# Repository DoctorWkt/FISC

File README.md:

# FISC: An 8-bit TTL CPU with a Stack Register

**Please note**: The FISC design has some major flaws. Rather than
fix them, I've incorporated the fixes into the next version of the
design: .

FISC is an 8-bit microseqenced CPU wth a 64K address space built from
discrete TTL-level components. It provides:

 + recursive **F**unctions,
 + **I**ndexed addressing and
 + **S**tack operations

as well as the usual load/store and arithmetic operations, comparisons,
branches and jumps.

The design uses 25 chips and has 8K of ROM, 56K of RAM and a UART.

## Documentation

The overall design of the CPU is covered in
[Docs/arch_overview.md](Docs/arch_overview.md), and some details
of the expected hardware implementation are in 
[Docs/fisc_implementation.md](Docs/fisc_implementation.md).

## Implementation

At present, I have:

 + a Perl CPU simulator, [csim](csim)
 + an assembler, [cas](cas)
 + a simple compiler, [clc](clc)
 + example assembly and higher-level programs in [Examples](Examples)
 + a Verilog design in [Verilog](Verilog)
 + a schematic in [Kicad/schematic.pdf](Kicad/schematic.pdf)

## Status of the CPU

**mid-June, 2020**: I've ordered PCBs and they have arrived and I've soldered
on all the components. The CPU passes most of the tests but I have an issue
with addition that I am still working on.

For more detail on progress, you can read my [journal](Docs/journal.md).

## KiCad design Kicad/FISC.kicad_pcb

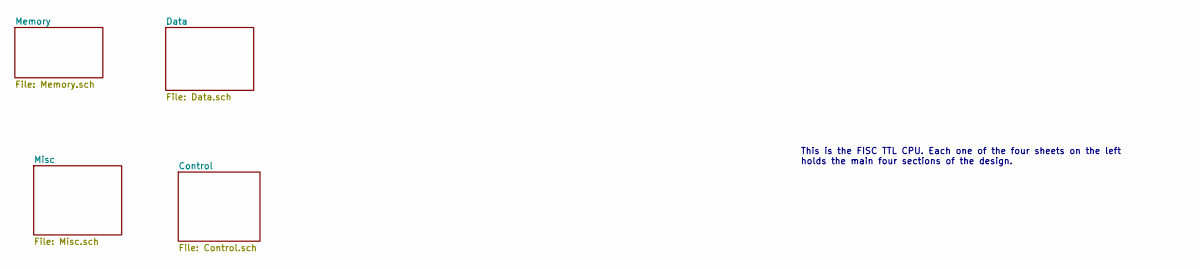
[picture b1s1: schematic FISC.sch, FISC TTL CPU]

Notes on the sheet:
This is the FISC TTL CPU. Each one of the four sheets on the left holds the main four sections of the design.

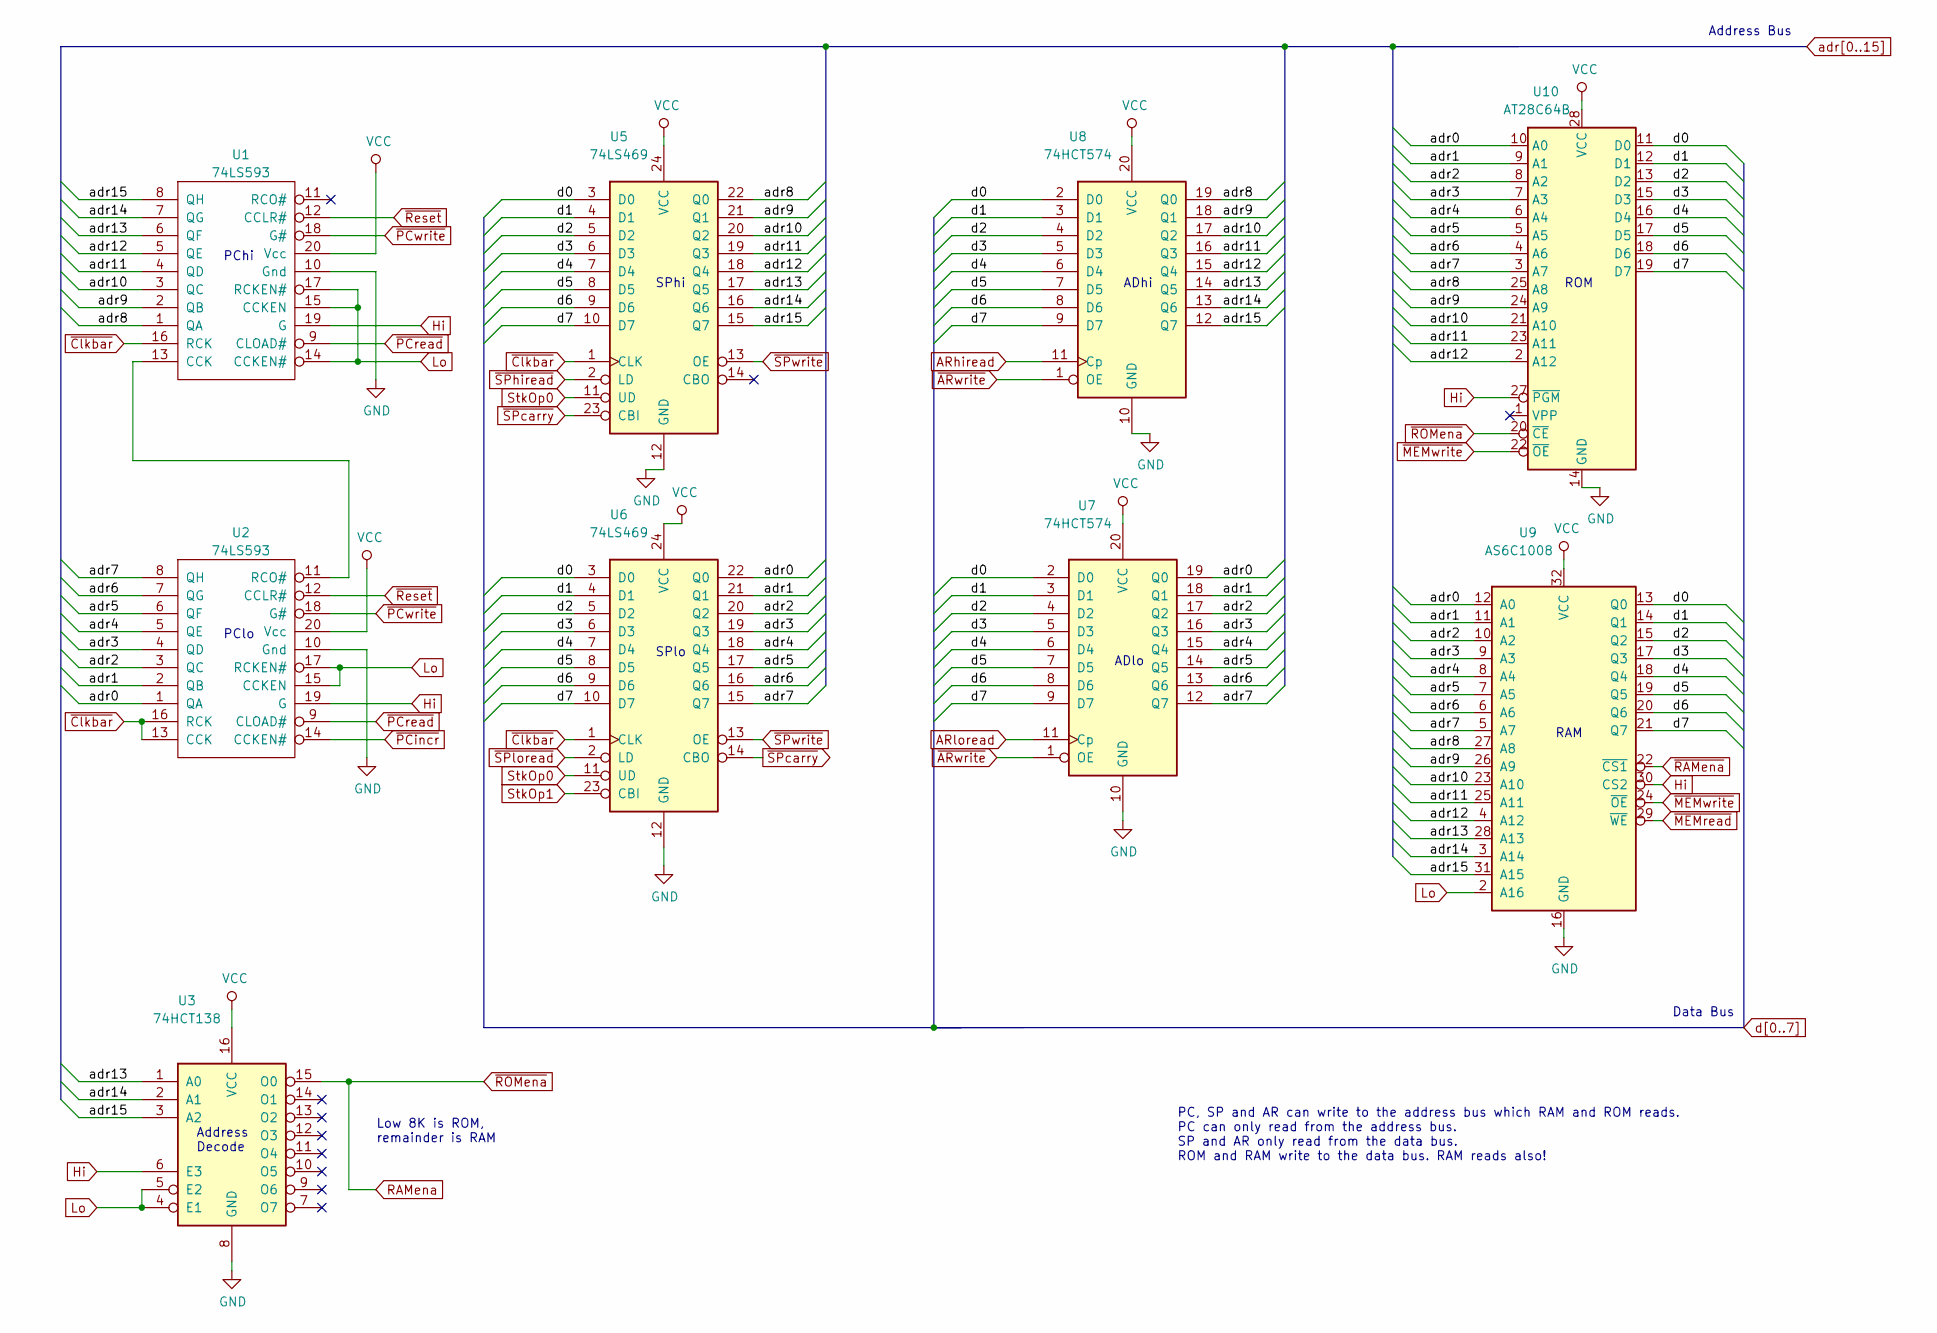
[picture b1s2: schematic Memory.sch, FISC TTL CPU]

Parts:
U1, U2: 74LS593; DIP-20_W7.62mm_Socket
U3: 74HCT138; SOIC-16_3.9x9.9mm_P1.27mm
U5, U6: 74LS469; DIP-24_W7.62mm
U7, U8: 74HCT574; SOIC-20W_7.5x12.8mm_P1.27mm
U9: AS6C1008; DIP-32_W15.24mm
U10: AT28C64B; DIP-28_W15.24mm

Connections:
ARhiread: U8.11 (Cp); also elsewhere on the board
ARloread: U7.11 (Cp); also elsewhere on the board
Hi: U1.19 (G), U1.20 (Vcc), U2.19 (G), U2.20 (Vcc), U3.6 (E3), U3.16 (VCC), U5.24 (VCC), U6.24 (VCC), U7.20 (VCC), U8.20 (VCC), U9.30 (CS2), U9.32 (VCC), U10.27 (~PGM), U10.28 (VCC); also elsewhere on the board
Lo: U1.10 (Gnd), U1.14 (CCKEN#), U1.15 (CCKEN), U1.17 (RCKEN#), U2.10 (Gnd), U2.15 (CCKEN), U2.17 (RCKEN#), U3.4 (E1), U3.5 (E2), U3.8 (GND), U5.12 (GND), U6.12 (GND), U7.10 (GND), U8.10 (GND), U9.2 (A16), U9.16 (GND), U10.14 (GND); also elsewhere on the board
unnamed: U1.13 (CCK), U2.11 (RCO#)
RAMena: U3.15 (O0), U10.20 (~CE); also elsewhere on the board
StkOp0: U5.11 (UD), U6.11 (UD); also elsewhere on the board
StkOp1: U6.23 (CBI); also elsewhere on the board
adr0: U2.1 (QA), U6.22 (Q0), U7.19 (Q0), U9.12 (A0), U10.10 (A0); also elsewhere on the board
adr1: U2.2 (QB), U6.21 (Q1), U7.18 (Q1), U9.11 (A1), U10.9 (A1); also elsewhere on the board
adr2: U2.3 (QC), U6.20 (Q2), U7.17 (Q2), U9.10 (A2), U10.8 (A2); also elsewhere on the board
adr3: U2.4 (QD), U6.19 (Q3), U7.16 (Q3), U9.9 (A3), U10.7 (A3); also elsewhere on the board
adr4: U2.5 (QE), U6.18 (Q4), U7.15 (Q4), U9.8 (A4), U10.6 (A4); also elsewhere on the board
adr5: U2.6 (QF), U6.17 (Q5), U7.14 (Q5), U9.7 (A5), U10.5 (A5); also elsewhere on the board
adr6: U2.7 (QG), U6.16 (Q6), U7.13 (Q6), U9.6 (A6), U10.4 (A6); also elsewhere on the board
adr7: U2.8 (QH), U6.15 (Q7), U7.12 (Q7), U9.5 (A7), U10.3 (A7); also elsewhere on the board
adr8: U1.1 (QA), U5.22 (Q0), U8.19 (Q0), U9.27 (A8), U10.25 (A8); also elsewhere on the board
adr9: U1.2 (QB), U5.21 (Q1), U8.18 (Q1), U9.26 (A9), U10.24 (A9); also elsewhere on the board
adr10: U1.3 (QC), U5.20 (Q2), U8.17 (Q2), U9.23 (A10), U10.21 (A10); also elsewhere on the board
adr11: U1.4 (QD), U5.19 (Q3), U8.16 (Q3), U9.25 (A11), U10.23 (A11); also elsewhere on the board
adr12: U1.5 (QE), U5.18 (Q4), U8.15 (Q4), U9.4 (A12), U10.2 (A12); also elsewhere on the board
adr13: U1.6 (QF), U3.1 (A0), U5.17 (Q5), U8.14 (Q5), U9.28 (A13); also elsewhere on the board
adr14: U1.7 (QG), U3.2 (A1), U5.16 (Q6), U8.13 (Q6), U9.3 (A14); also elsewhere on the board
adr15: U1.8 (QH), U3.3 (A2), U5.15 (Q7), U8.12 (Q7), U9.31 (A15); also elsewhere on the board
d0: U5.3 (D0), U6.3 (D0), U7.2 (D0), U8.2 (D0), U9.13 (Q0), U10.11 (D0); also elsewhere on the board
d1: U5.4 (D1), U6.4 (D1), U7.3 (D1), U8.3 (D1), U9.14 (Q1), U10.12 (D1); also elsewhere on the board
d2: U5.5 (D2), U6.5 (D2), U7.4 (D2), U8.4 (D2), U9.15 (Q2), U10.13 (D2); also elsewhere on the board
d3: U5.6 (D3), U6.6 (D3), U7.5 (D3), U8.5 (D3), U9.17 (Q3), U10.15 (D3); also elsewhere on the board
d4: U5.7 (D4), U6.7 (D4), U7.6 (D4), U8.6 (D4), U9.18 (Q4), U10.16 (D4); also elsewhere on the board
d5: U5.8 (D5), U6.8 (D5), U7.7 (D5), U8.7 (D5), U9.19 (Q5), U10.17 (D5); also elsewhere on the board
d6: U5.9 (D6), U6.9 (D6), U7.8 (D6), U8.8 (D6), U9.20 (Q6), U10.18 (D6); also elsewhere on the board
d7: U5.10 (D7), U6.10 (D7), U7.9 (D7), U8.9 (D7), U9.21 (Q7), U10.19 (D7); also elsewhere on the board
~ARwrite: U7.1 (OE), U8.1 (OE); also elsewhere on the board
~Clkbar: U1.16 (RCK), U2.13 (CCK), U2.16 (RCK), U5.1 (CLK), U6.1 (CLK); also elsewhere on the board
~MEMread: U9.29 (~WE); also elsewhere on the board
~MEMwrite: U9.24 (~OE), U10.22 (~OE); also elsewhere on the board
~PCincr: U2.14 (CCKEN#); also elsewhere on the board
~PCread: U1.9 (CLOAD#), U2.9 (CLOAD#); also elsewhere on the board
~PCwrite: U1.18 (G#), U2.18 (G#); also elsewhere on the board
~RAMena: U9.22 (~CS1); also elsewhere on the board
~Reset: U1.12 (CCLR#), U2.12 (CCLR#); also elsewhere on the board
~SPcarry: U5.23 (CBI), U6.14 (CBO)
~SPhiread: U5.2 (LD); also elsewhere on the board
~SPloread: U6.2 (LD); also elsewhere on the board
~SPwrite: U5.13 (OE), U6.13 (OE); also elsewhere on the board

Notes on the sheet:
RAM
ROM
ADhi
ADlo
SPhi
SPlo
PChi
PClo
Address Decode
Address Bus
Data Bus
Low 8K is ROM, remainder is RAM
PC, SP and AR can write to the address bus which RAM and ROM reads. PC can only read from the address bus. SP and AR only read from the data bus. ROM and RAM write to the data bus. RAM reads also!

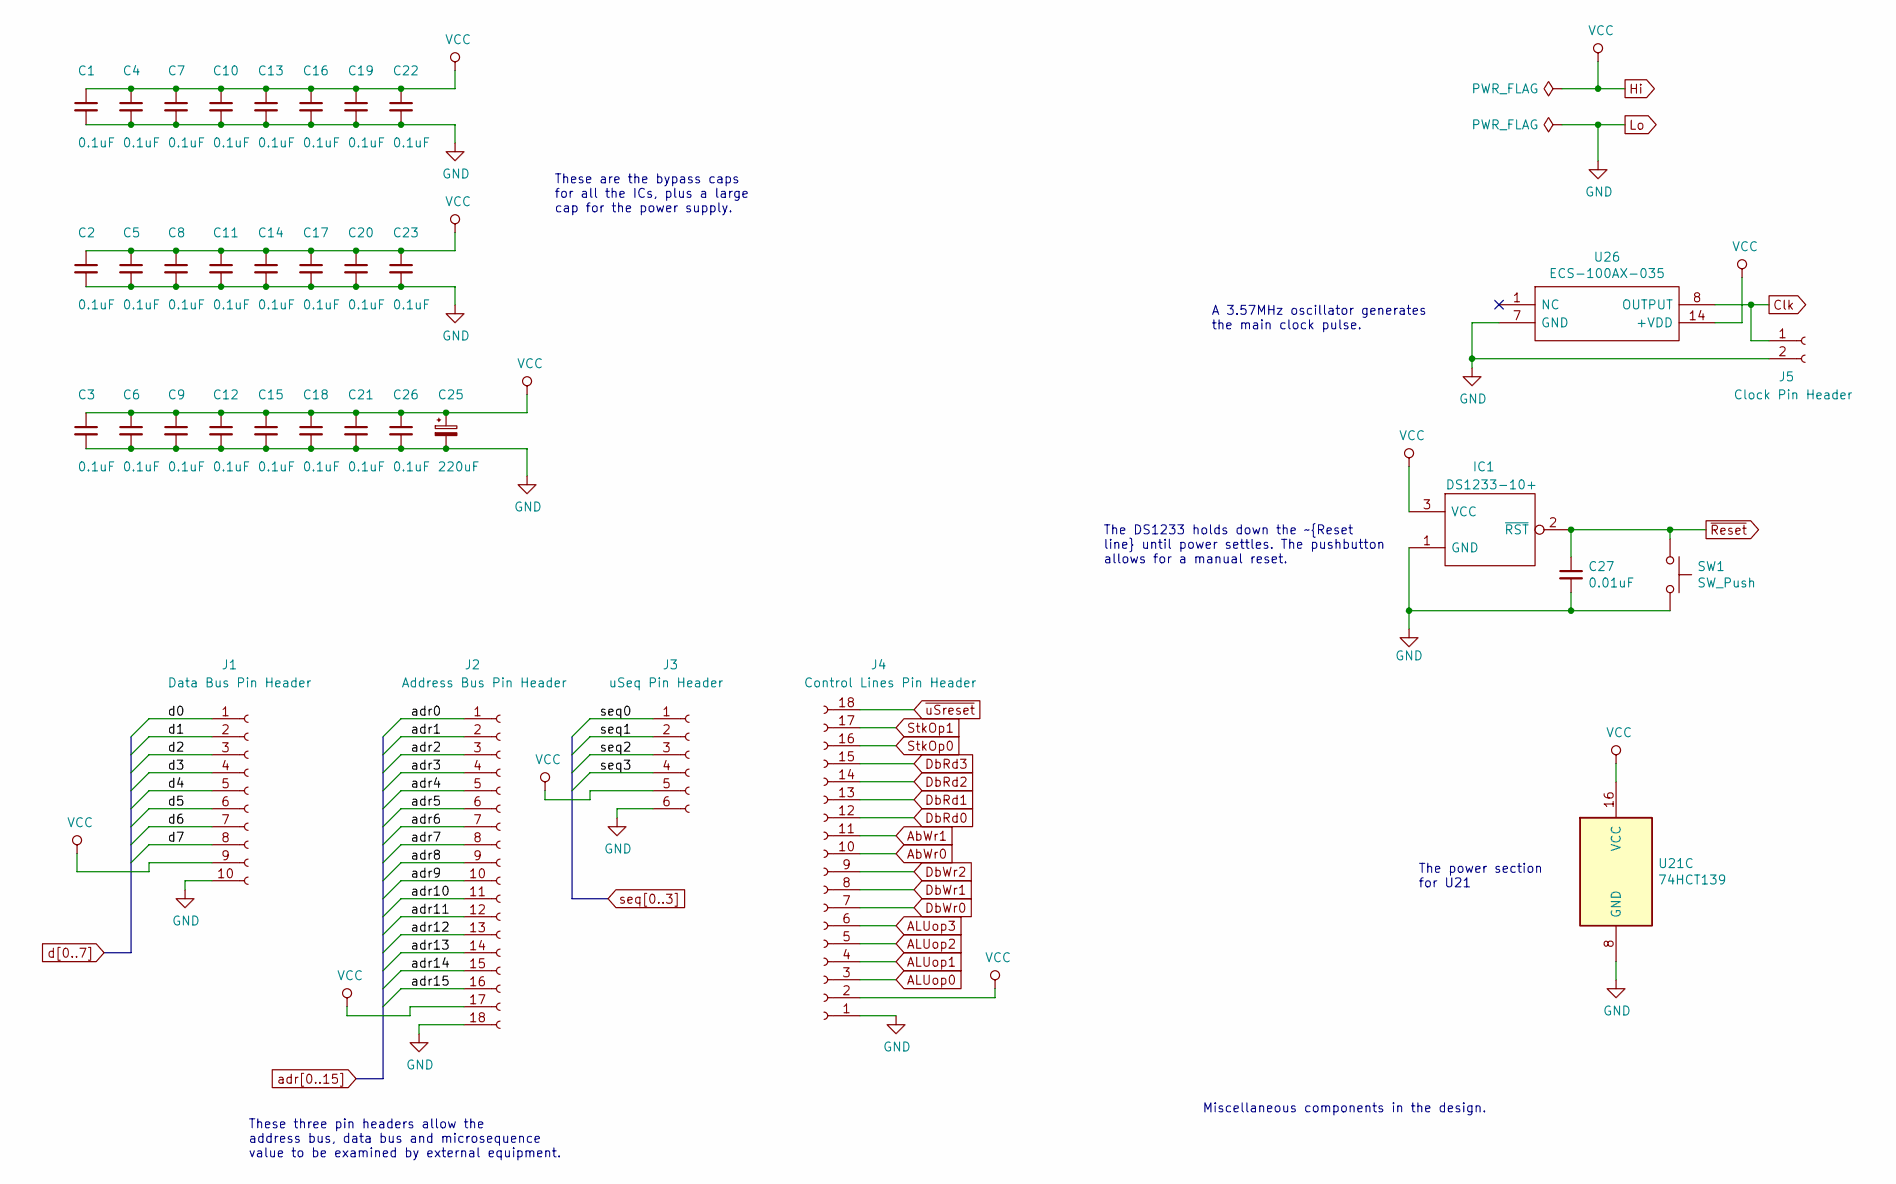
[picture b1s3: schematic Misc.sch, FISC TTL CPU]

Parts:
C1, C2, C3, C4, C5, C6, C7, C8, C9, C10, C11, C12, C13, C14, C15, C16, C17, C18, C19, C20, C21, C22, C23, C26: 0.1uF; C_0603_1608Metric_Pad1.05x0.95mm_HandSolder
C25: 220uF; CP_Radial_D8.0mm_P5.00mm
C27: 0.01uF; C_0603_1608Metric_Pad1.05x0.95mm_HandSolder
IC1: DS1233-10+; TO-92; Manufacturer_Part_Number DS1233-10+; Mouser Part Number 700-DS1233-10
J1: Data Bus Pin Header; PinSocket_1x10_P2.54mm_Vertical
J2: Address Bus Pin Header; PinSocket_1x18_P2.54mm_Vertical
J3: uSeq Pin Header; PinSocket_1x06_P2.54mm_Vertical
J4: Control Lines Pin Header; PinSocket_1x18_P2.54mm_Vertical
J5: Clock Pin Header; PinSocket_1x02_P2.54mm_Vertical
SW1: SW_Push; Push_E-Switch_KS01Q01
U21: 74HCT139; SOIC-16_3.9x9.9mm_P1.27mm
U26: ECS-100AX-035; Oscillator_DIP-14; Manufacturer_Part_Number QX14T50B1.843200B50TT

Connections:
ALUop0: J4.3; also elsewhere on the board
ALUop1: J4.4; also elsewhere on the board
ALUop2: J4.5; also elsewhere on the board
ALUop3: J4.6; also elsewhere on the board
AbWr0: J4.10; also elsewhere on the board
AbWr1: J4.11; also elsewhere on the board
Clk: J5.1, U26.8 (OUTPUT); also elsewhere on the board
DbRd0: J4.12; also elsewhere on the board
DbRd1: J4.13; also elsewhere on the board
DbRd2: J4.14; also elsewhere on the board
DbRd3: J4.15; also elsewhere on the board
DbWr0: J4.7; also elsewhere on the board
DbWr1: J4.8; also elsewhere on the board
DbWr2: J4.9; also elsewhere on the board
Hi: C1.1, C2.1, C3.1, C4.1, C5.1, C6.1, C7.1, C8.1, C9.1, C10.1, C11.1, C12.1, C13.1, C14.1, C15.1, C16.1, C17.1, C18.1, C19.1, C20.1, C21.1, C22.1, C23.1, C25.1, C26.1, IC1.3 (VCC), J1.9, J2.17, J3.5, J4.2, U21.16 (VCC), U26.14 (+VDD); also elsewhere on the board
Lo: C1.2, C2.2, C3.2, C4.2, C5.2, C6.2, C7.2, C8.2, C9.2, C10.2, C11.2, C12.2, C13.2, C14.2, C15.2, C16.2, C17.2, C18.2, C19.2, C20.2, C21.2, C22.2, C23.2, C25.2, C26.2, C27.2, IC1.1 (GND), J1.10, J2.18, J3.6, J4.1, J5.2, SW1.2, U21.8 (GND), U26.7 (GND); also elsewhere on the board
StkOp0: J4.16; also elsewhere on the board
StkOp1: J4.17; also elsewhere on the board
adr0: J2.1; also elsewhere on the board
adr1: J2.2; also elsewhere on the board
adr2: J2.3; also elsewhere on the board
adr3: J2.4; also elsewhere on the board
adr4: J2.5; also elsewhere on the board
adr5: J2.6; also elsewhere on the board
adr6: J2.7; also elsewhere on the board
adr7: J2.8; also elsewhere on the board
adr8: J2.9; also elsewhere on the board
adr9: J2.10; also elsewhere on the board
adr10: J2.11; also elsewhere on the board
adr11: J2.12; also elsewhere on the board
adr12: J2.13; also elsewhere on the board
adr13: J2.14; also elsewhere on the board
adr14: J2.15; also elsewhere on the board
adr15: J2.16; also elsewhere on the board
d0: J1.1; also elsewhere on the board
d1: J1.2; also elsewhere on the board
d2: J1.3; also elsewhere on the board
d3: J1.4; also elsewhere on the board
d4: J1.5; also elsewhere on the board
d5: J1.6; also elsewhere on the board
d6: J1.7; also elsewhere on the board
d7: J1.8; also elsewhere on the board
seq0: J3.1; also elsewhere on the board
seq1: J3.2; also elsewhere on the board
seq2: J3.3; also elsewhere on the board
seq3: J3.4; also elsewhere on the board
~Reset: C27.1, IC1.2 (~RST), SW1.1; also elsewhere on the board
~uSreset: J4.18; also elsewhere on the board

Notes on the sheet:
A 3.57MHz oscillator generates the main clock pulse.
The DS1233 holds down the ~Reset line until power settles. The pushbutton allows for a manual reset.
The power section for U21
These are the bypass caps for all the ICs, plus a large cap for the power supply.
These three pin headers allow the address bus, data bus and microsequence value to be examined by external equipment.
Miscellaneous components in the design.

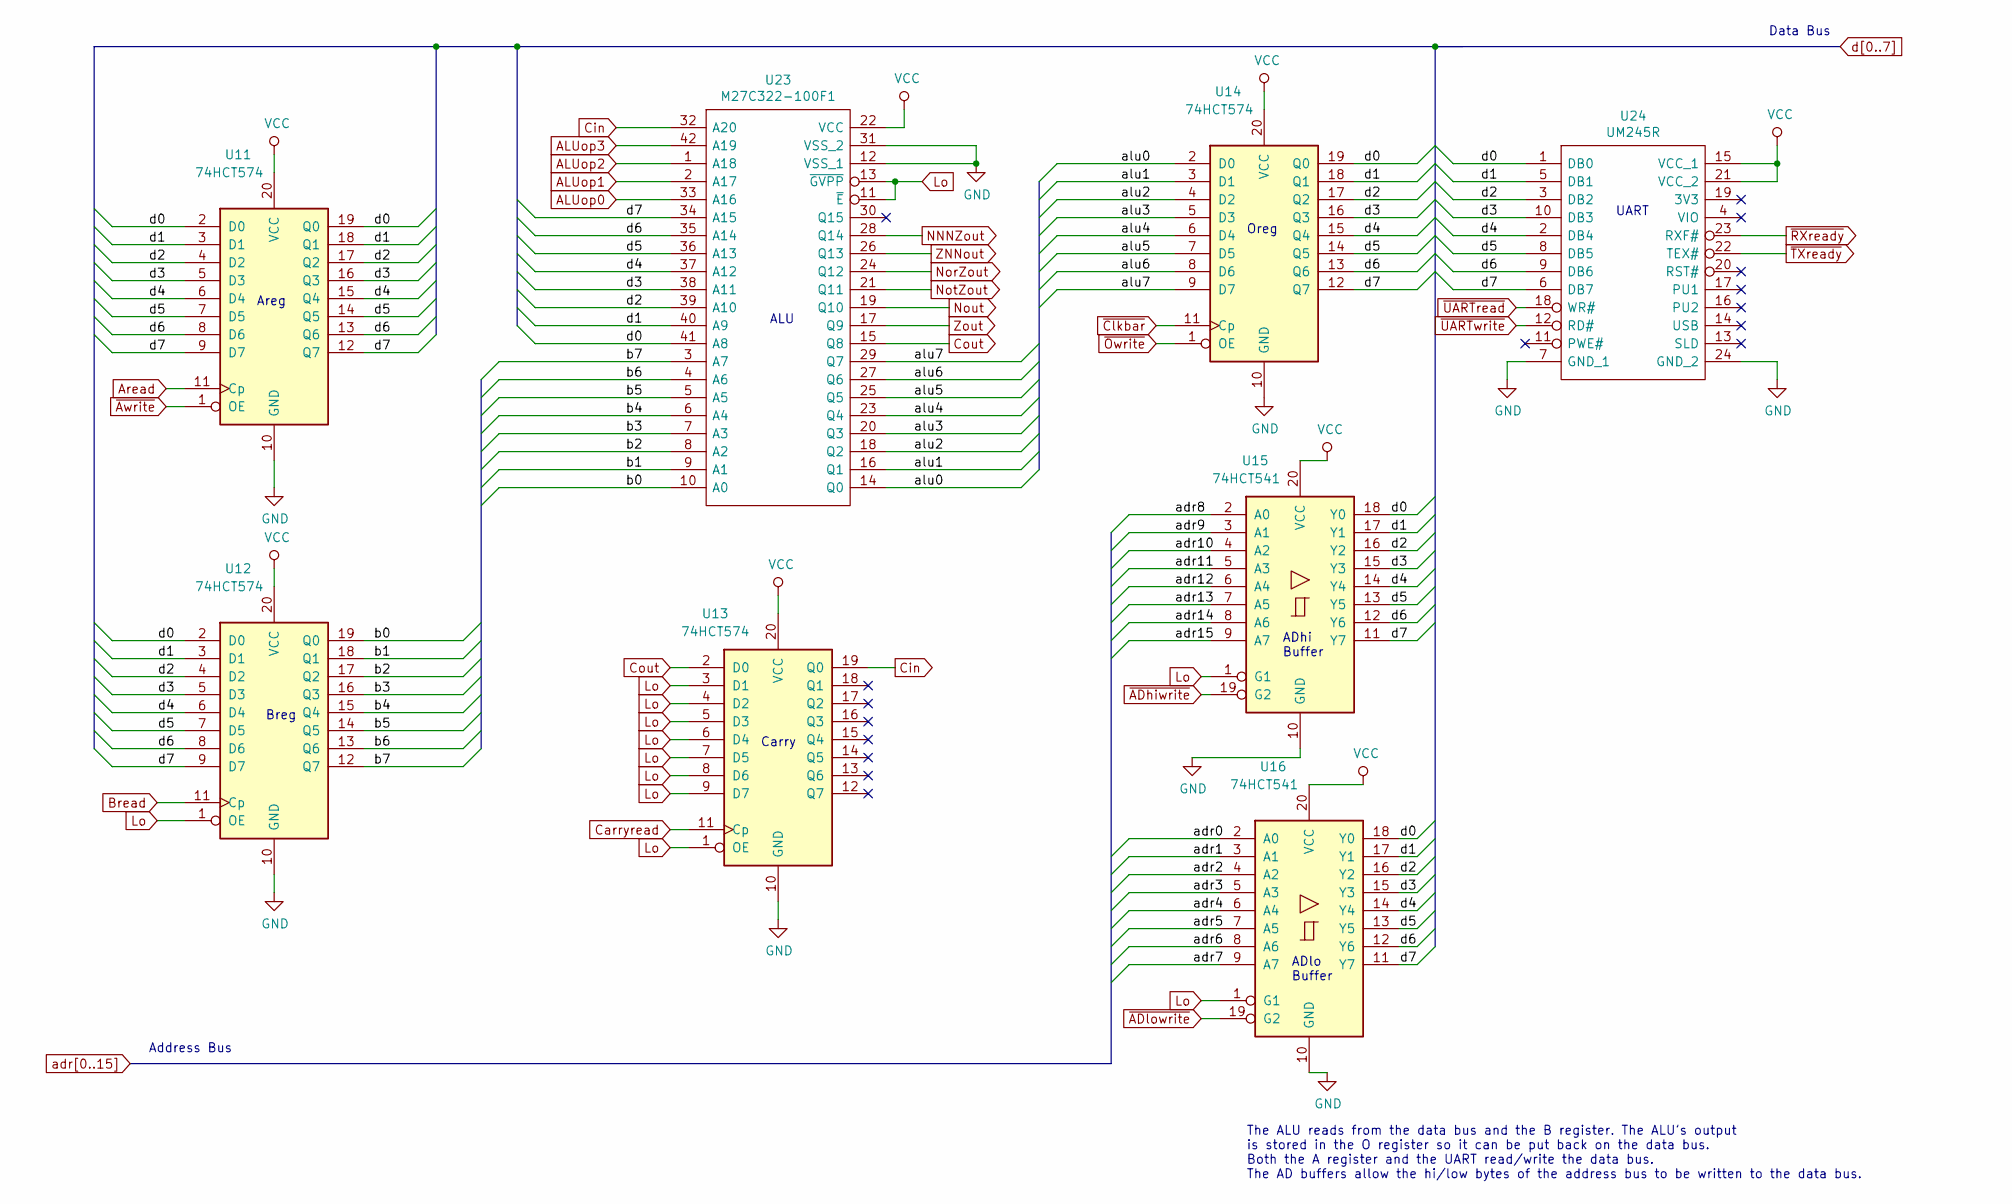
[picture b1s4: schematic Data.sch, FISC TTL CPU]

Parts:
U11, U12, U13, U14: 74HCT574; SOIC-20W_7.5x12.8mm_P1.27mm
U15, U16: 74HCT541; SOIC-20W_7.5x12.8mm_P1.27mm
U23: M27C322-100F1; DIP-42_W15.24mm; Manufacturer_Part_Number M27C322-100F1; Mouser Part Number 511-M27C322-10F
U24: UM245R; DIP-24_W15.24mm_Socket; Manufacturer_Part_Number UM245R; Mouser Part Number 895-UM245R

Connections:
/Data/alu0: U14.2 (D0), U23.14 (Q0)
/Data/alu1: U14.3 (D1), U23.16 (Q1)
/Data/alu2: U14.4 (D2), U23.18 (Q2)
/Data/alu3: U14.5 (D3), U23.20 (Q3)
/Data/alu4: U14.6 (D4), U23.23 (Q4)
/Data/alu5: U14.7 (D5), U23.25 (Q5)
/Data/alu6: U14.8 (D6), U23.27 (Q6)
/Data/alu7: U14.9 (D7), U23.29 (Q7)
/Data/b0: U12.19 (Q0), U23.10 (A0)
/Data/b1: U12.18 (Q1), U23.9 (A1)
/Data/b2: U12.17 (Q2), U23.8 (A2)
/Data/b3: U12.16 (Q3), U23.7 (A3)
/Data/b4: U12.15 (Q4), U23.6 (A4)
/Data/b5: U12.14 (Q5), U23.5 (A5)
/Data/b6: U12.13 (Q6), U23.4 (A6)
/Data/b7: U12.12 (Q7), U23.3 (A7)
ALUop0: U23.33 (A16); also elsewhere on the board
ALUop1: U23.2 (A17); also elsewhere on the board
ALUop2: U23.1 (A18); also elsewhere on the board
ALUop3: U23.42 (A19); also elsewhere on the board
Aread: U11.11 (Cp); also elsewhere on the board
Bread: U12.11 (Cp); also elsewhere on the board
Carryread: U13.11 (Cp); also elsewhere on the board
Cin: U13.19 (Q0), U23.32 (A20)
Cout: U13.2 (D0), U23.15 (Q8)
Hi: U11.20 (VCC), U12.20 (VCC), U13.20 (VCC), U14.20 (VCC), U15.20 (VCC), U16.20 (VCC), U23.22 (VCC), U24.15 (VCC_1), U24.21 (VCC_2); also elsewhere on the board
Lo: U11.10 (GND), U12.1 (OE), U12.10 (GND), U13.1 (OE), U13.3 (D1), U13.4 (D2), U13.5 (D3), U13.6 (D4), U13.7 (D5), U13.8 (D6), U13.9 (D7), U13.10 (GND), U14.10 (GND), U15.1 (G1), U15.10 (GND), U16.1 (G1), U16.10 (GND), U23.11 (~E), U23.12 (VSS_1), U23.13 (~GVPP), U23.31 (VSS_2), U24.7 (GND_1), U24.24 (GND_2); also elsewhere on the board
NNNZout: U23.28 (Q14); also elsewhere on the board
NorZout: U23.24 (Q12); also elsewhere on the board
NotZout: U23.21 (Q11); also elsewhere on the board
Nout: U23.19 (Q10); also elsewhere on the board
ZNNout: U23.26 (Q13); also elsewhere on the board
Zout: U23.17 (Q9); also elsewhere on the board
adr0: U16.2 (A0); also elsewhere on the board
adr1: U16.3 (A1); also elsewhere on the board
adr2: U16.4 (A2); also elsewhere on the board
adr3: U16.5 (A3); also elsewhere on the board
adr4: U16.6 (A4); also elsewhere on the board
adr5: U16.7 (A5); also elsewhere on the board
adr6: U16.8 (A6); also elsewhere on the board
adr7: U16.9 (A7); also elsewhere on the board
adr8: U15.2 (A0); also elsewhere on the board
adr9: U15.3 (A1); also elsewhere on the board
adr10: U15.4 (A2); also elsewhere on the board
adr11: U15.5 (A3); also elsewhere on the board
adr12: U15.6 (A4); also elsewhere on the board
adr13: U15.7 (A5); also elsewhere on the board
adr14: U15.8 (A6); also elsewhere on the board
adr15: U15.9 (A7); also elsewhere on the board
d0: U11.2 (D0), U11.19 (Q0), U12.2 (D0), U14.19 (Q0), U15.18 (Y0), U16.18 (Y0), U23.41 (A8), U24.1 (DB0); also elsewhere on the board
d1: U11.3 (D1), U11.18 (Q1), U12.3 (D1), U14.18 (Q1), U15.17 (Y1), U16.17 (Y1), U23.40 (A9), U24.5 (DB1); also elsewhere on the board
d2: U11.4 (D2), U11.17 (Q2), U12.4 (D2), U14.17 (Q2), U15.16 (Y2), U16.16 (Y2), U23.39 (A10), U24.3 (DB2); also elsewhere on the board
d3: U11.5 (D3), U11.16 (Q3), U12.5 (D3), U14.16 (Q3), U15.15 (Y3), U16.15 (Y3), U23.38 (A11), U24.10 (DB3); also elsewhere on the board
d4: U11.6 (D4), U11.15 (Q4), U12.6 (D4), U14.15 (Q4), U15.14 (Y4), U16.14 (Y4), U23.37 (A12), U24.2 (DB4); also elsewhere on the board
d5: U11.7 (D5), U11.14 (Q5), U12.7 (D5), U14.14 (Q5), U15.13 (Y5), U16.13 (Y5), U23.36 (A13), U24.8 (DB5); also elsewhere on the board
d6: U11.8 (D6), U11.13 (Q6), U12.8 (D6), U14.13 (Q6), U15.12 (Y6), U16.12 (Y6), U23.35 (A14), U24.9 (DB6); also elsewhere on the board
d7: U11.9 (D7), U11.12 (Q7), U12.9 (D7), U14.12 (Q7), U15.11 (Y7), U16.11 (Y7), U23.34 (A15), U24.6 (DB7); also elsewhere on the board
~ADhiwrite: U15.19 (G2); also elsewhere on the board
~ADlowrite: U16.19 (G2); also elsewhere on the board
~Awrite: U11.1 (OE); also elsewhere on the board
~Clkbar: U14.11 (Cp); also elsewhere on the board
~Owrite: U14.1 (OE); also elsewhere on the board
~RXready: U24.23 (RXF#); also elsewhere on the board
~TXready: U24.22 (TEX#); also elsewhere on the board
~UARTread: U24.18 (WR#); also elsewhere on the board
~UARTwrite: U24.12 (RD#); also elsewhere on the board

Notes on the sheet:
Areg
Carry
UART
Oreg
ALU
Breg
ADhi Buffer
ADlo Buffer
Data Bus
Address Bus
The ALU reads from the data bus and the B register. The ALU's output is stored in the O register so it can be put back on the data bus. Both the A register and the UART read/write the data bus. The AD buffers allow the hi/low bytes of the address bus to be written to the data bus.

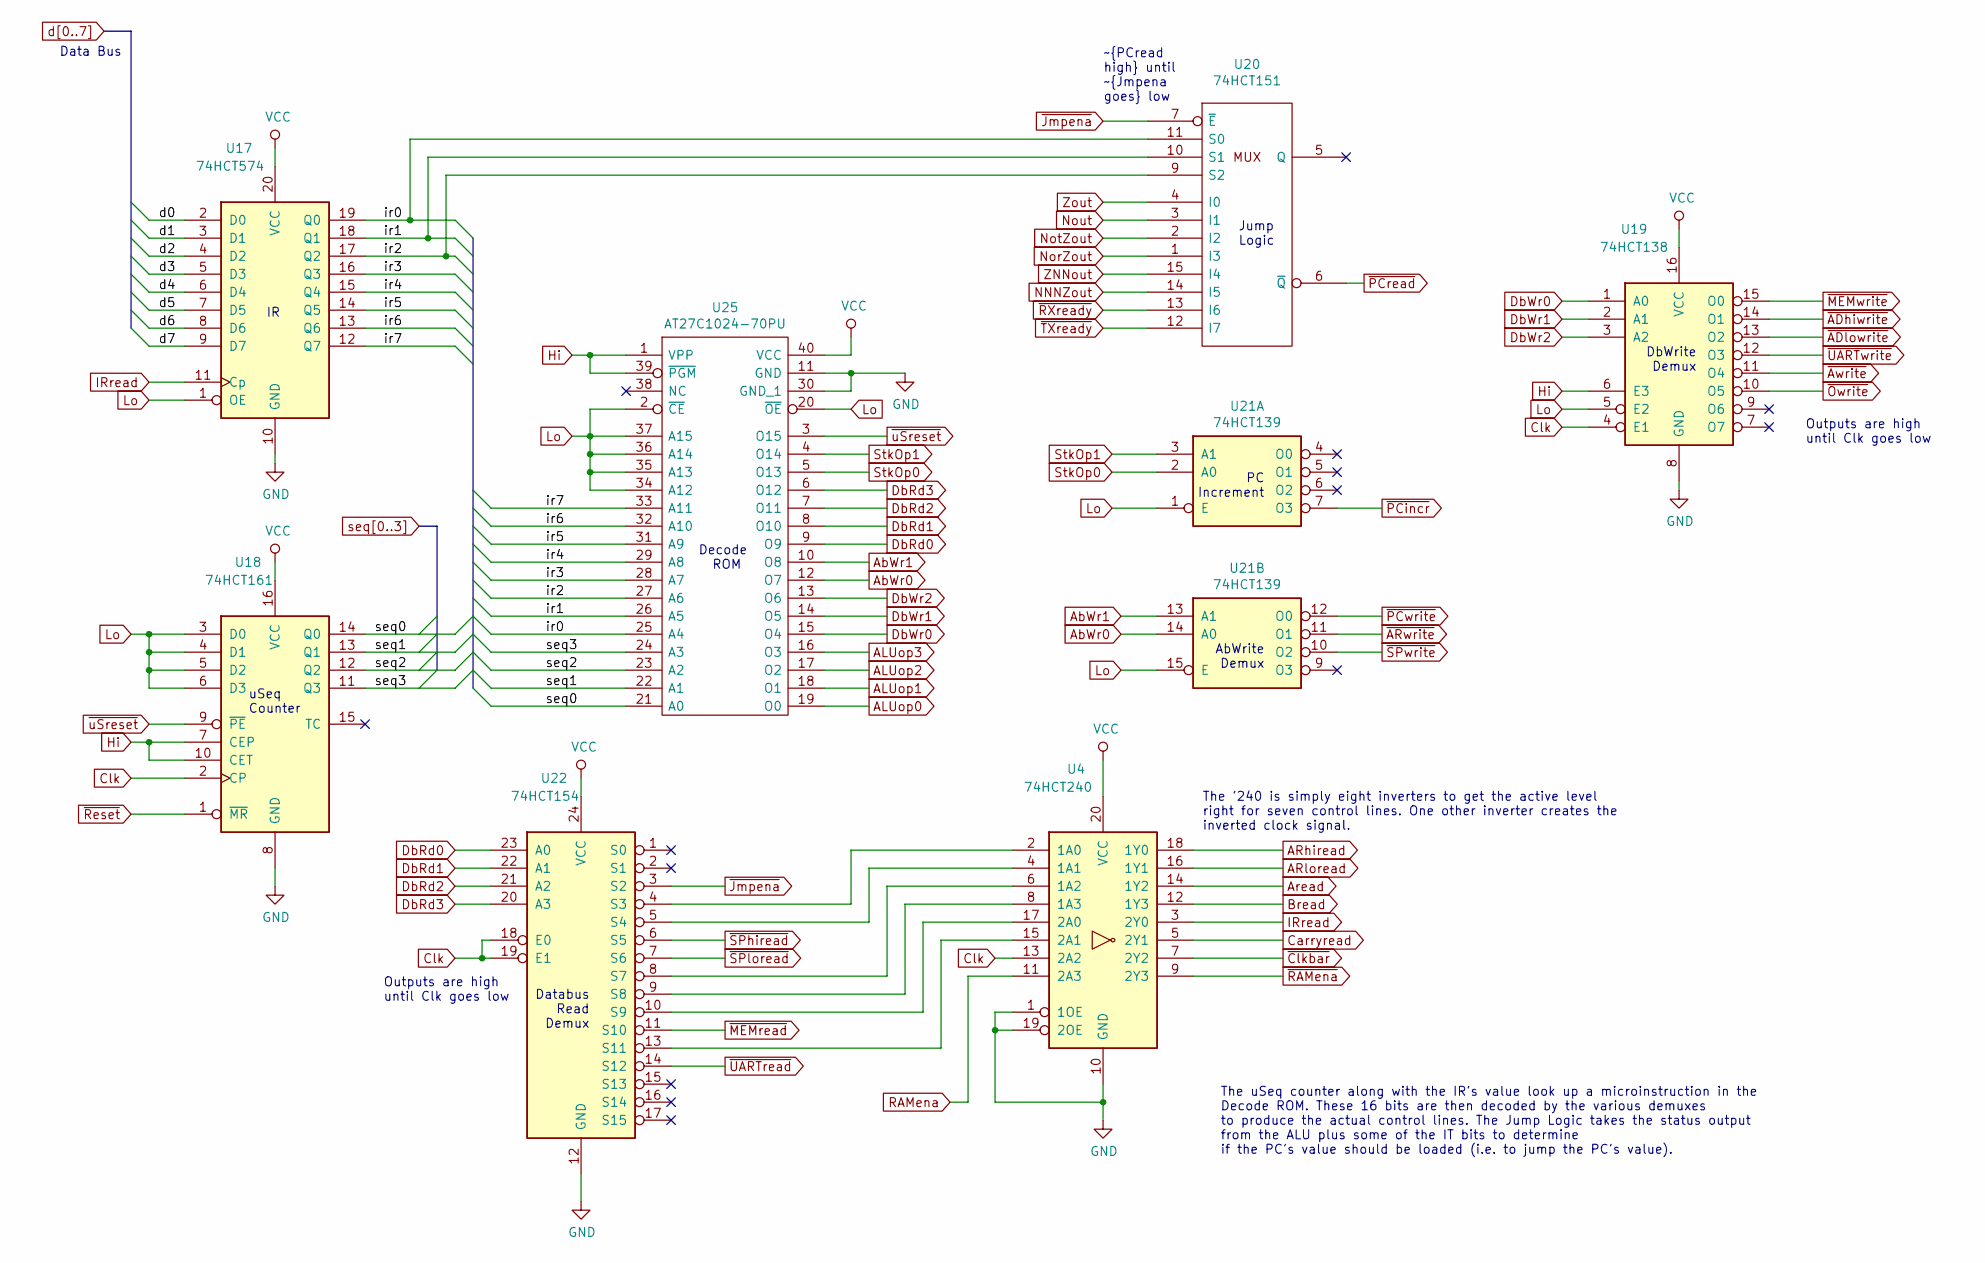
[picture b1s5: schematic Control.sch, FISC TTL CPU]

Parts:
U4: 74HCT240; SOIC-20W_7.5x12.8mm_P1.27mm
U17: 74HCT574; SOIC-20W_7.5x12.8mm_P1.27mm
U18: 74HCT161; SOIC-16_3.9x9.9mm_P1.27mm
U19: 74HCT138; SOIC-16_3.9x9.9mm_P1.27mm
U20: 74HCT151; SOIC-16_3.9x9.9mm_P1.27mm
U21: 74HCT139; SOIC-16_3.9x9.9mm_P1.27mm
U22: 74HCT154; SOIC-24W_7.5x15.4mm_P1.27mm
U25: AT27C1024-70PU; DIP-40_W15.24mm; Manufacturer_Part_Number AT27C1024-70PU; Mouser Part Number 556-AT27C102470PU

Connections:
/Control/ir0: U17.19 (Q0), U20.11 (S0), U25.25 (A4)
/Control/ir1: U17.18 (Q1), U20.10 (S1), U25.26 (A5)
/Control/ir2: U17.17 (Q2), U20.9 (S2), U25.27 (A6)
/Control/ir3: U17.16 (Q3), U25.28 (A7)
/Control/ir4: U17.15 (Q4), U25.29 (A8)
/Control/ir5: U17.14 (Q5), U25.31 (A9)
/Control/ir6: U17.13 (Q6), U25.32 (A10)
/Control/ir7: U17.12 (Q7), U25.33 (A11)
ALUop0: U25.19 (O0); also elsewhere on the board
ALUop1: U25.18 (O1); also elsewhere on the board
ALUop2: U25.17 (O2); also elsewhere on the board
ALUop3: U25.16 (O3); also elsewhere on the board
ARhiread: U4.18 (1Y0); also elsewhere on the board
ARloread: U4.16 (1Y1); also elsewhere on the board
AbWr0: U21.14 (A0), U25.12 (O7); also elsewhere on the board
AbWr1: U21.13 (A1), U25.10 (O8); also elsewhere on the board
Aread: U4.14 (1Y2); also elsewhere on the board
Bread: U4.12 (1Y3); also elsewhere on the board
Carryread: U4.5 (2Y1); also elsewhere on the board
Clk: U4.13 (2A2), U18.2 (CP), U19.4 (E1), U22.18 (E0), U22.19 (E1); also elsewhere on the board
DbRd0: U22.23 (A0), U25.9 (O9); also elsewhere on the board
DbRd1: U22.22 (A1), U25.8 (O10); also elsewhere on the board
DbRd2: U22.21 (A2), U25.7 (O11); also elsewhere on the board
DbRd3: U22.20 (A3), U25.6 (O12); also elsewhere on the board
DbWr0: U19.1 (A0), U25.15 (O4); also elsewhere on the board
DbWr1: U19.2 (A1), U25.14 (O5); also elsewhere on the board
DbWr2: U19.3 (A2), U25.13 (O6); also elsewhere on the board
Hi: U4.20 (VCC), U17.20 (VCC), U18.7 (CEP), U18.10 (CET), U18.16 (VCC), U19.6 (E3), U19.16 (VCC), U20.16 (VCC), U22.24 (VCC), U25.1 (VPP), U25.39 (~PGM), U25.40 (VCC); also elsewhere on the board
IRread: U4.3 (2Y0), U17.11 (Cp)
Lo: U4.1 (1OE), U4.10 (GND), U4.19 (2OE), U17.1 (OE), U17.10 (GND), U18.3 (D0), U18.4 (D1), U18.5 (D2), U18.6 (D3), U18.8 (GND), U19.5 (E2), U19.8 (GND), U20.8 (GND), U21.1 (E), U21.15 (E), U22.12 (GND), U25.2 (~CE), U25.11 (GND), U25.20 (~OE), U25.30 (GND_1), U25.34 (A12), U25.35 (A13), U25.36 (A14), U25.37 (A15); also elsewhere on the board
NNNZout: U20.14 (I5); also elsewhere on the board
unnamed: U4.2 (1A0), U22.4 (S3)
unnamed: U4.4 (1A1), U22.5 (S4)
unnamed: U4.6 (1A2), U22.8 (S7)
unnamed: U4.8 (1A3), U22.9 (S8)
unnamed: U4.17 (2A0), U22.10 (S9)
unnamed: U4.15 (2A1), U22.13 (S11)
NorZout: U20.1 (I3); also elsewhere on the board
NotZout: U20.2 (I2); also elsewhere on the board
Nout: U20.3 (I1); also elsewhere on the board
RAMena: U4.11 (2A3); also elsewhere on the board
StkOp0: U21.2 (A0), U25.5 (O13); also elsewhere on the board
StkOp1: U21.3 (A1), U25.4 (O14); also elsewhere on the board
ZNNout: U20.15 (I4); also elsewhere on the board
Zout: U20.4 (I0); also elsewhere on the board
d0: U17.2 (D0); also elsewhere on the board
d1: U17.3 (D1); also elsewhere on the board
d2: U17.4 (D2); also elsewhere on the board
d3: U17.5 (D3); also elsewhere on the board
d4: U17.6 (D4); also elsewhere on the board
d5: U17.7 (D5); also elsewhere on the board
d6: U17.8 (D6); also elsewhere on the board
d7: U17.9 (D7); also elsewhere on the board
seq0: U18.14 (Q0), U25.21 (A0); also elsewhere on the board
seq1: U18.13 (Q1), U25.22 (A1); also elsewhere on the board
seq2: U18.12 (Q2), U25.23 (A2); also elsewhere on the board
seq3: U18.11 (Q3), U25.24 (A3); also elsewhere on the board
~ADhiwrite: U19.14 (O1); also elsewhere on the board
~ADlowrite: U19.13 (O2); also elsewhere on the board
~ARwrite: U21.11 (O1); also elsewhere on the board
~Awrite: U19.11 (O4); also elsewhere on the board
~Clkbar: U4.7 (2Y2); also elsewhere on the board
~Jmpena: U20.7 (~E), U22.3 (S2)
~MEMread: U22.11 (S10); also elsewhere on the board
~MEMwrite: U19.15 (O0); also elsewhere on the board
~Owrite: U19.10 (O5); also elsewhere on the board
~PCincr: U21.7 (O3); also elsewhere on the board
~PCread: U20.6 (~Q); also elsewhere on the board
~PCwrite: U21.12 (O0); also elsewhere on the board
~RAMena: U4.9 (2Y3); also elsewhere on the board
~RXready: U20.13 (I6); also elsewhere on the board
~Reset: U18.1 (~MR); also elsewhere on the board
~SPhiread: U22.6 (S5); also elsewhere on the board
~SPloread: U22.7 (S6); also elsewhere on the board
~SPwrite: U21.10 (O2); also elsewhere on the board
~TXready: U20.12 (I7); also elsewhere on the board
~UARTread: U22.14 (S12); also elsewhere on the board
~UARTwrite: U19.12 (O3); also elsewhere on the board
~uSreset: U18.9 (~PE), U25.3 (O15); also elsewhere on the board

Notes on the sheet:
uSeq Counter
Decode ROM
Jump Logic
DbWrite Demux
AbWrite Demux
Databus Read Demux
Data Bus
Outputs are high until Clk goes low
~PCread high until ~Jmpena goes low
The uSeq counter along with the IR's value look up a microinstruction in the Decode ROM. These 16 bits are then decoded by the various demuxes to produce the actual control lines. The Jump Logic takes the status output from the ALU plus some of the IT bits to determine if the PC's value should be l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
The '240 is simply eight inverters to get the active level right for seven control lines. One other inverter creates the inverted clock signal.
PC Increment

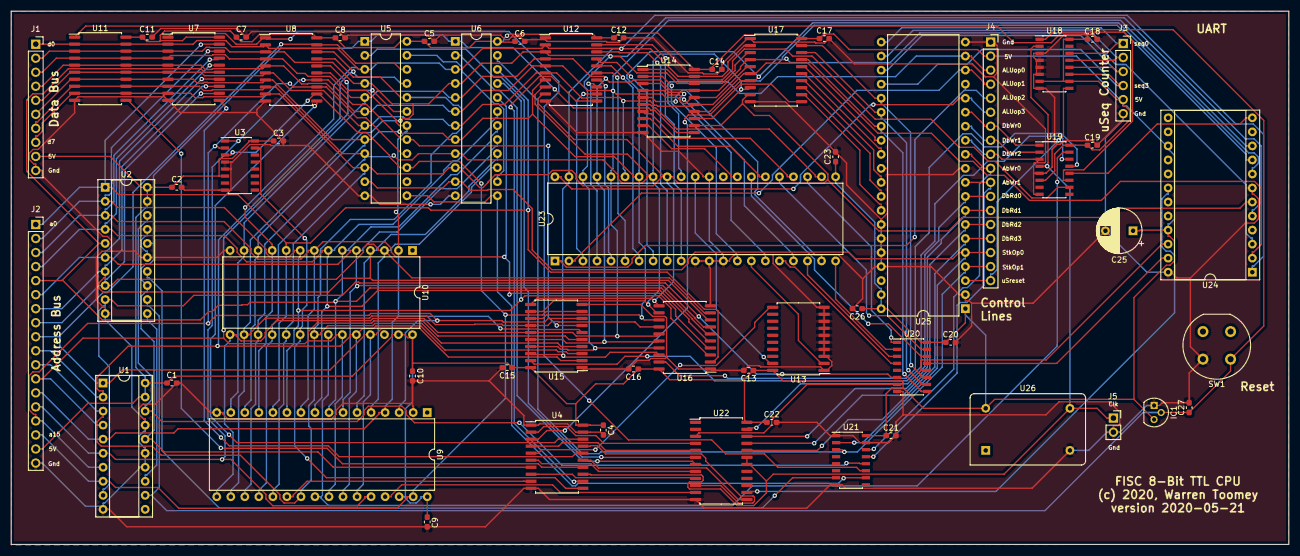
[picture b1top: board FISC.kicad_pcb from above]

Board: 2 copper layers, 231.3 x 96.5 mm, 59 parts (0 on the bottom side), 115 nets.

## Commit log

2020-05-16 First few files to go up to repo.
2020-05-16 First version to be uploaded to the Github repository.
2020-05-16 Fixed markdown in README.
2020-05-17 Made a slight update to the PCB layout.
2020-05-17 Redid the track layout.
2020-05-17 Typo in README.md
2020-05-20 Added the equ pseudo-op. Rearranged the PCB layout.
2020-05-20 Updated the schematic. Added some more labels to the PCB silk screen.
2020-05-20 Slight PCB update: more DIP sockets.
2020-05-20 Got the `clc` compiler to work.
    For this, I had to replace the logical shift right ALU operation
    with an arithmetic shift right. I added a `make compile` action
    in the `Makefile` so you can see the compiler work.
2020-05-20 Wiring mistake with the O register in the Verilog version.
2020-05-21 Lots of changes.
    I found a few wiring mistakes in the schematic and fixed them up.
    I added microcode instructions to allow B to be copied out to A,
    to the UART and to memory. I added a lot of `mem = mem op B`
    instructions. I added some examples to test the above. I redid the
    PCB layout and added copper pours.
2020-05-26 Fixed I/O handling in csim simulator. Created gerber files.
2020-05-26 Updated the README.md with the current project status.
2020-05-27 Starting to build the thing.
2020-05-28 Tested the 74LS469 chip.
2020-06-11 Fixed up a bug in csim and a wiring error in the databus write demux.
    Also, updated my journal with the build details to date.
2020-06-11 Added a picture to the journal.
2020-06-12 Fixed the broken B register in the build.
2020-06-14 Several improvements.
    I've imported the gen_ucode from FISC2 as it has better error detection.
    I've added some better debug output to csim. I have added a few more
    instructions to the microcode. Finally, one new test for the new
    instructions.
2020-06-15 I've finally grokked the 74LS469 device.
    And it is not good news: read the Docs/journal.md
    for more details.
2020-06-15 Better journal wording.
2020-06-15 Journal typo fixed.
2020-06-16 I made a mistake with the 74LS469 description; fixed.
2020-06-17 Updated the journal with more details.
2020-06-18 More journal entries plus some debugging instructions.
2020-06-18 Another journal entry.
2020-06-20 More journal entries.
2020-06-20 Another journal update.
2020-06-25 I have a workaround for the stack pointer problem.
    See the journal for details.
2020-06-25 Clean up journal table
2020-06-25 Journal typos fixed.
2020-07-05 FISC development now ended, and switched over to FISC2.
    I've finished the development of FISC and changed over to its
    successor, ![FISC2](https://github.com/DoctorWkt/2FISC).

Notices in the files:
Kicad/FISC.kicad_pcb:
(c) 2020, Warren Toomey
